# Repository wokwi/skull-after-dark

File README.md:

# The Skull CTF - After Dark Edition

https://skullctf.com/

PCB License: [CC BY-SA 4.0](https://creativecommons.org/licenses/by-sa/4.0/)

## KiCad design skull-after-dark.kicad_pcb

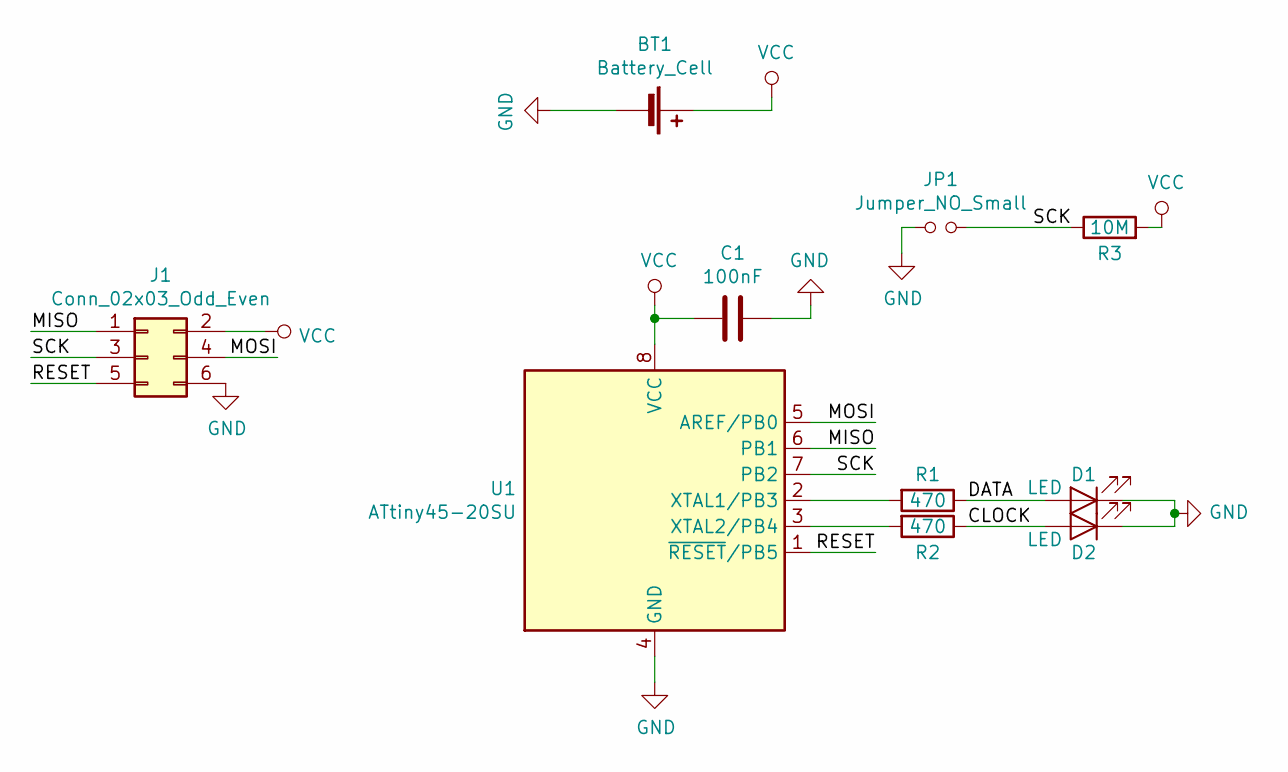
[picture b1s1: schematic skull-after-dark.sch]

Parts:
BT1: Battery_Cell; BatteryHolder_Keystone_3002_1x2032
C1: 100nF; C_0603_1608Metric
D1, D2: LED; LED_D5.0mm
J1: Conn_02x03_Odd_Even; PinHeader_2x03_P2.54mm_Vertical_SMD
JP1: Jumper_NO_Small; finger-grill
R1, R2: 470; R_0603_1608Metric
R3: 10M; R_0603_1608Metric
U1: ATtiny45-20SU; SOIJ-8_5.3x5.3mm_P1.27mm

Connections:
/CLOCK: D2.2 (A), R2.1
/DATA: D1.2 (A), R1.1
/MISO: J1.1, U1.6 (PB1)
/MOSI: J1.4, U1.5 (AREF/PB0)
/RESET: J1.5, U1.1 (~RESET~/PB5)
/SCK: J1.3, JP1.2, R3.1, U1.7 (PB2)
GND: BT1.2 (-), C1.1, D1.1 (K), D2.1 (K), J1.6, JP1.1, U1.4 (GND)
unnamed: R1.2, U1.2 (XTAL1/PB3)
unnamed: R2.2, U1.3 (XTAL2/PB4)
VCC: BT1.1 (+), C1.2, J1.2, R3.2, U1.8 (VCC)

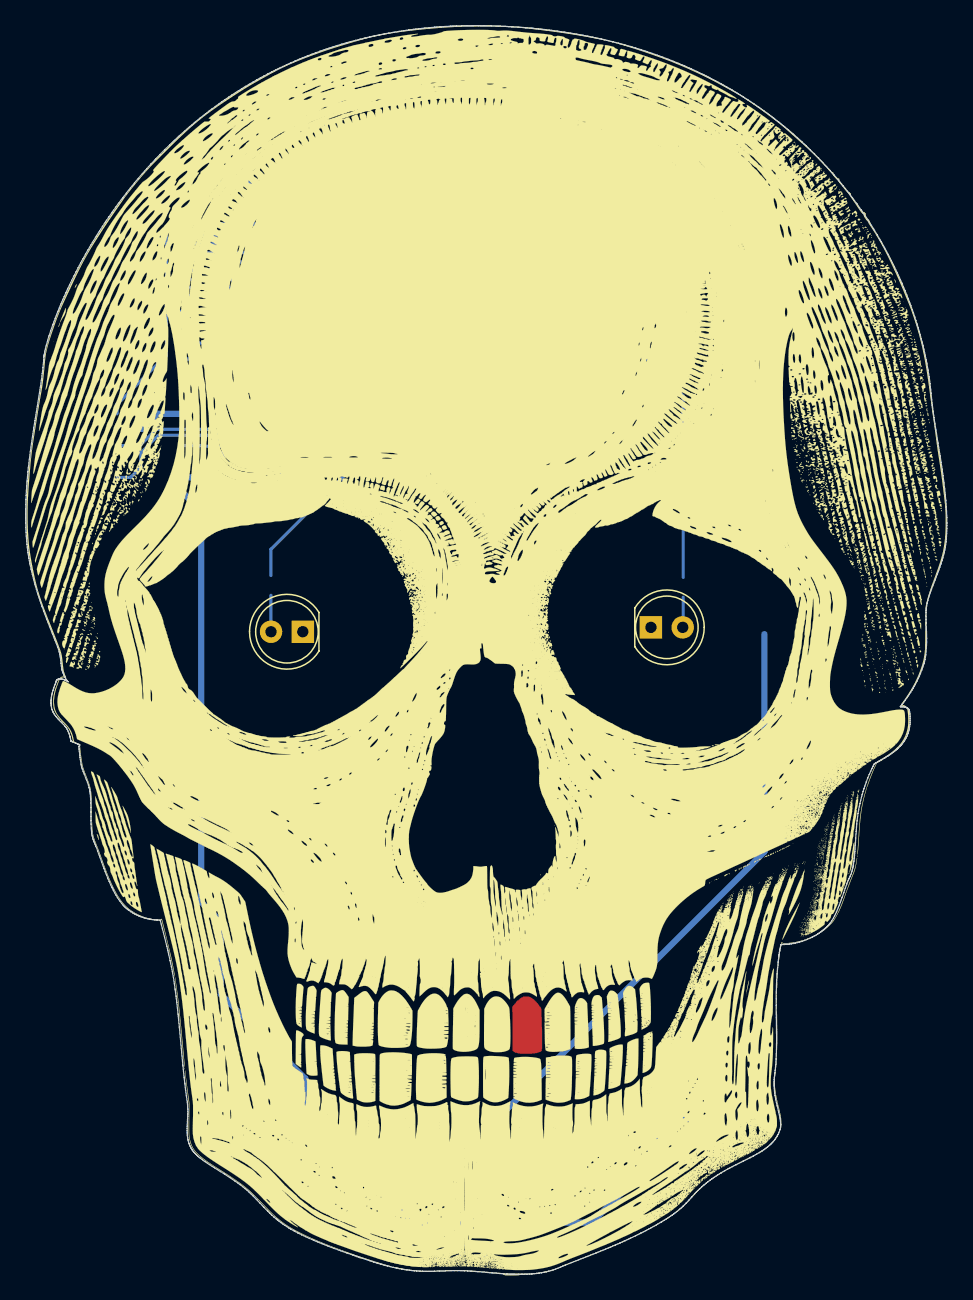
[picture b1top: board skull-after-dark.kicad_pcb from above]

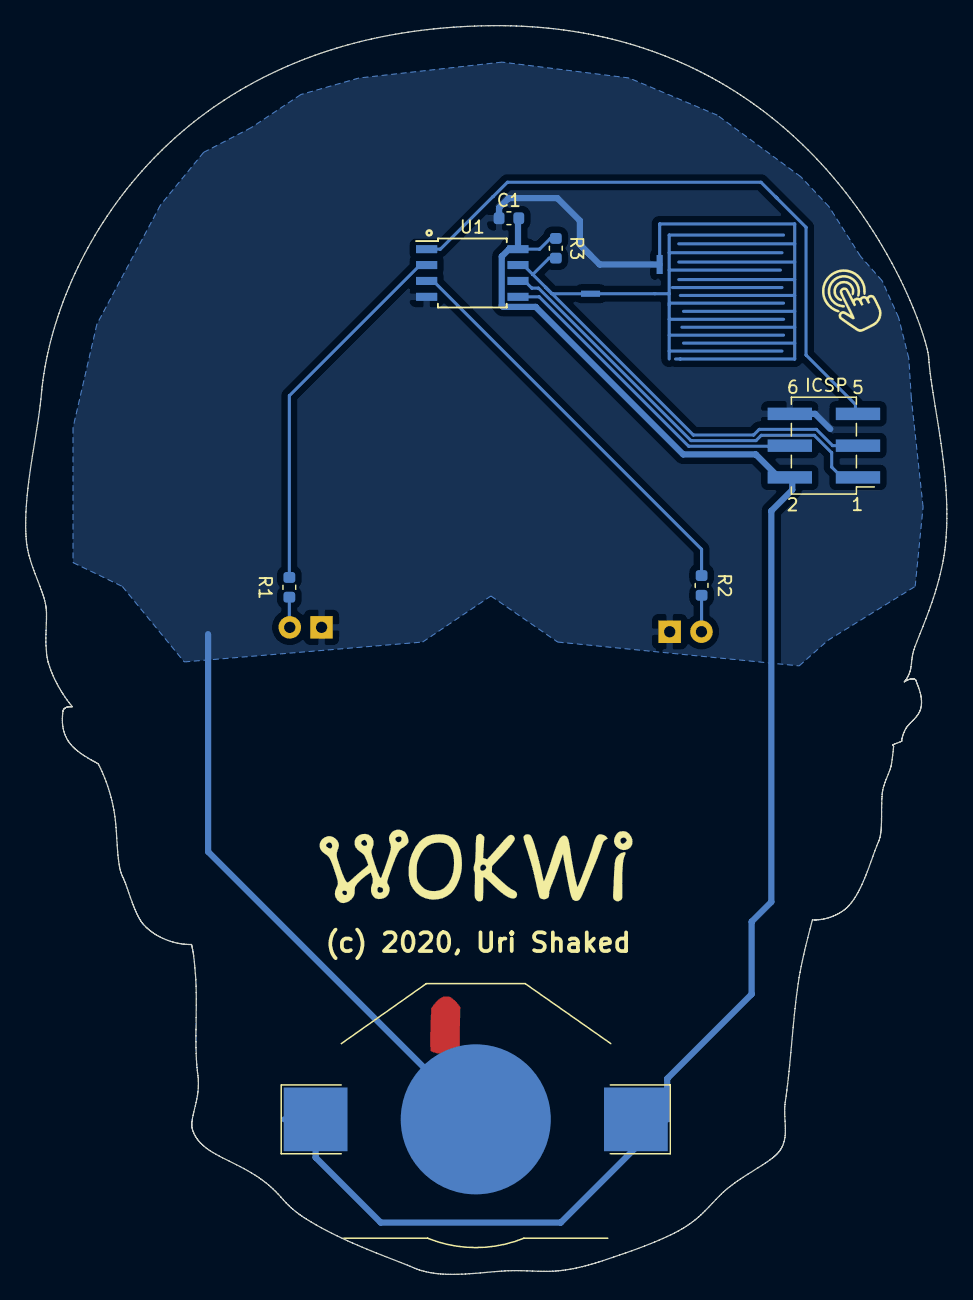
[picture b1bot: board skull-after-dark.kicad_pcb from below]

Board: 2 copper layers, 73.6 x 99.8 mm, 13 parts (10 on the bottom side), 10 nets.

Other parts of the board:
Ref**: Val**; skull-2-prep
Ref**#2: Val**; wokwi
Ref**#3: Val**; skull-touch

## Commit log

2020-12-12 After dark! 🌑
2020-12-16 Elongate pads for SMD programming header
    3.15mm -> 3.55mm

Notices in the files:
skull-after-dark.kicad_pcb:
(c) 2020, Uri Shaked
